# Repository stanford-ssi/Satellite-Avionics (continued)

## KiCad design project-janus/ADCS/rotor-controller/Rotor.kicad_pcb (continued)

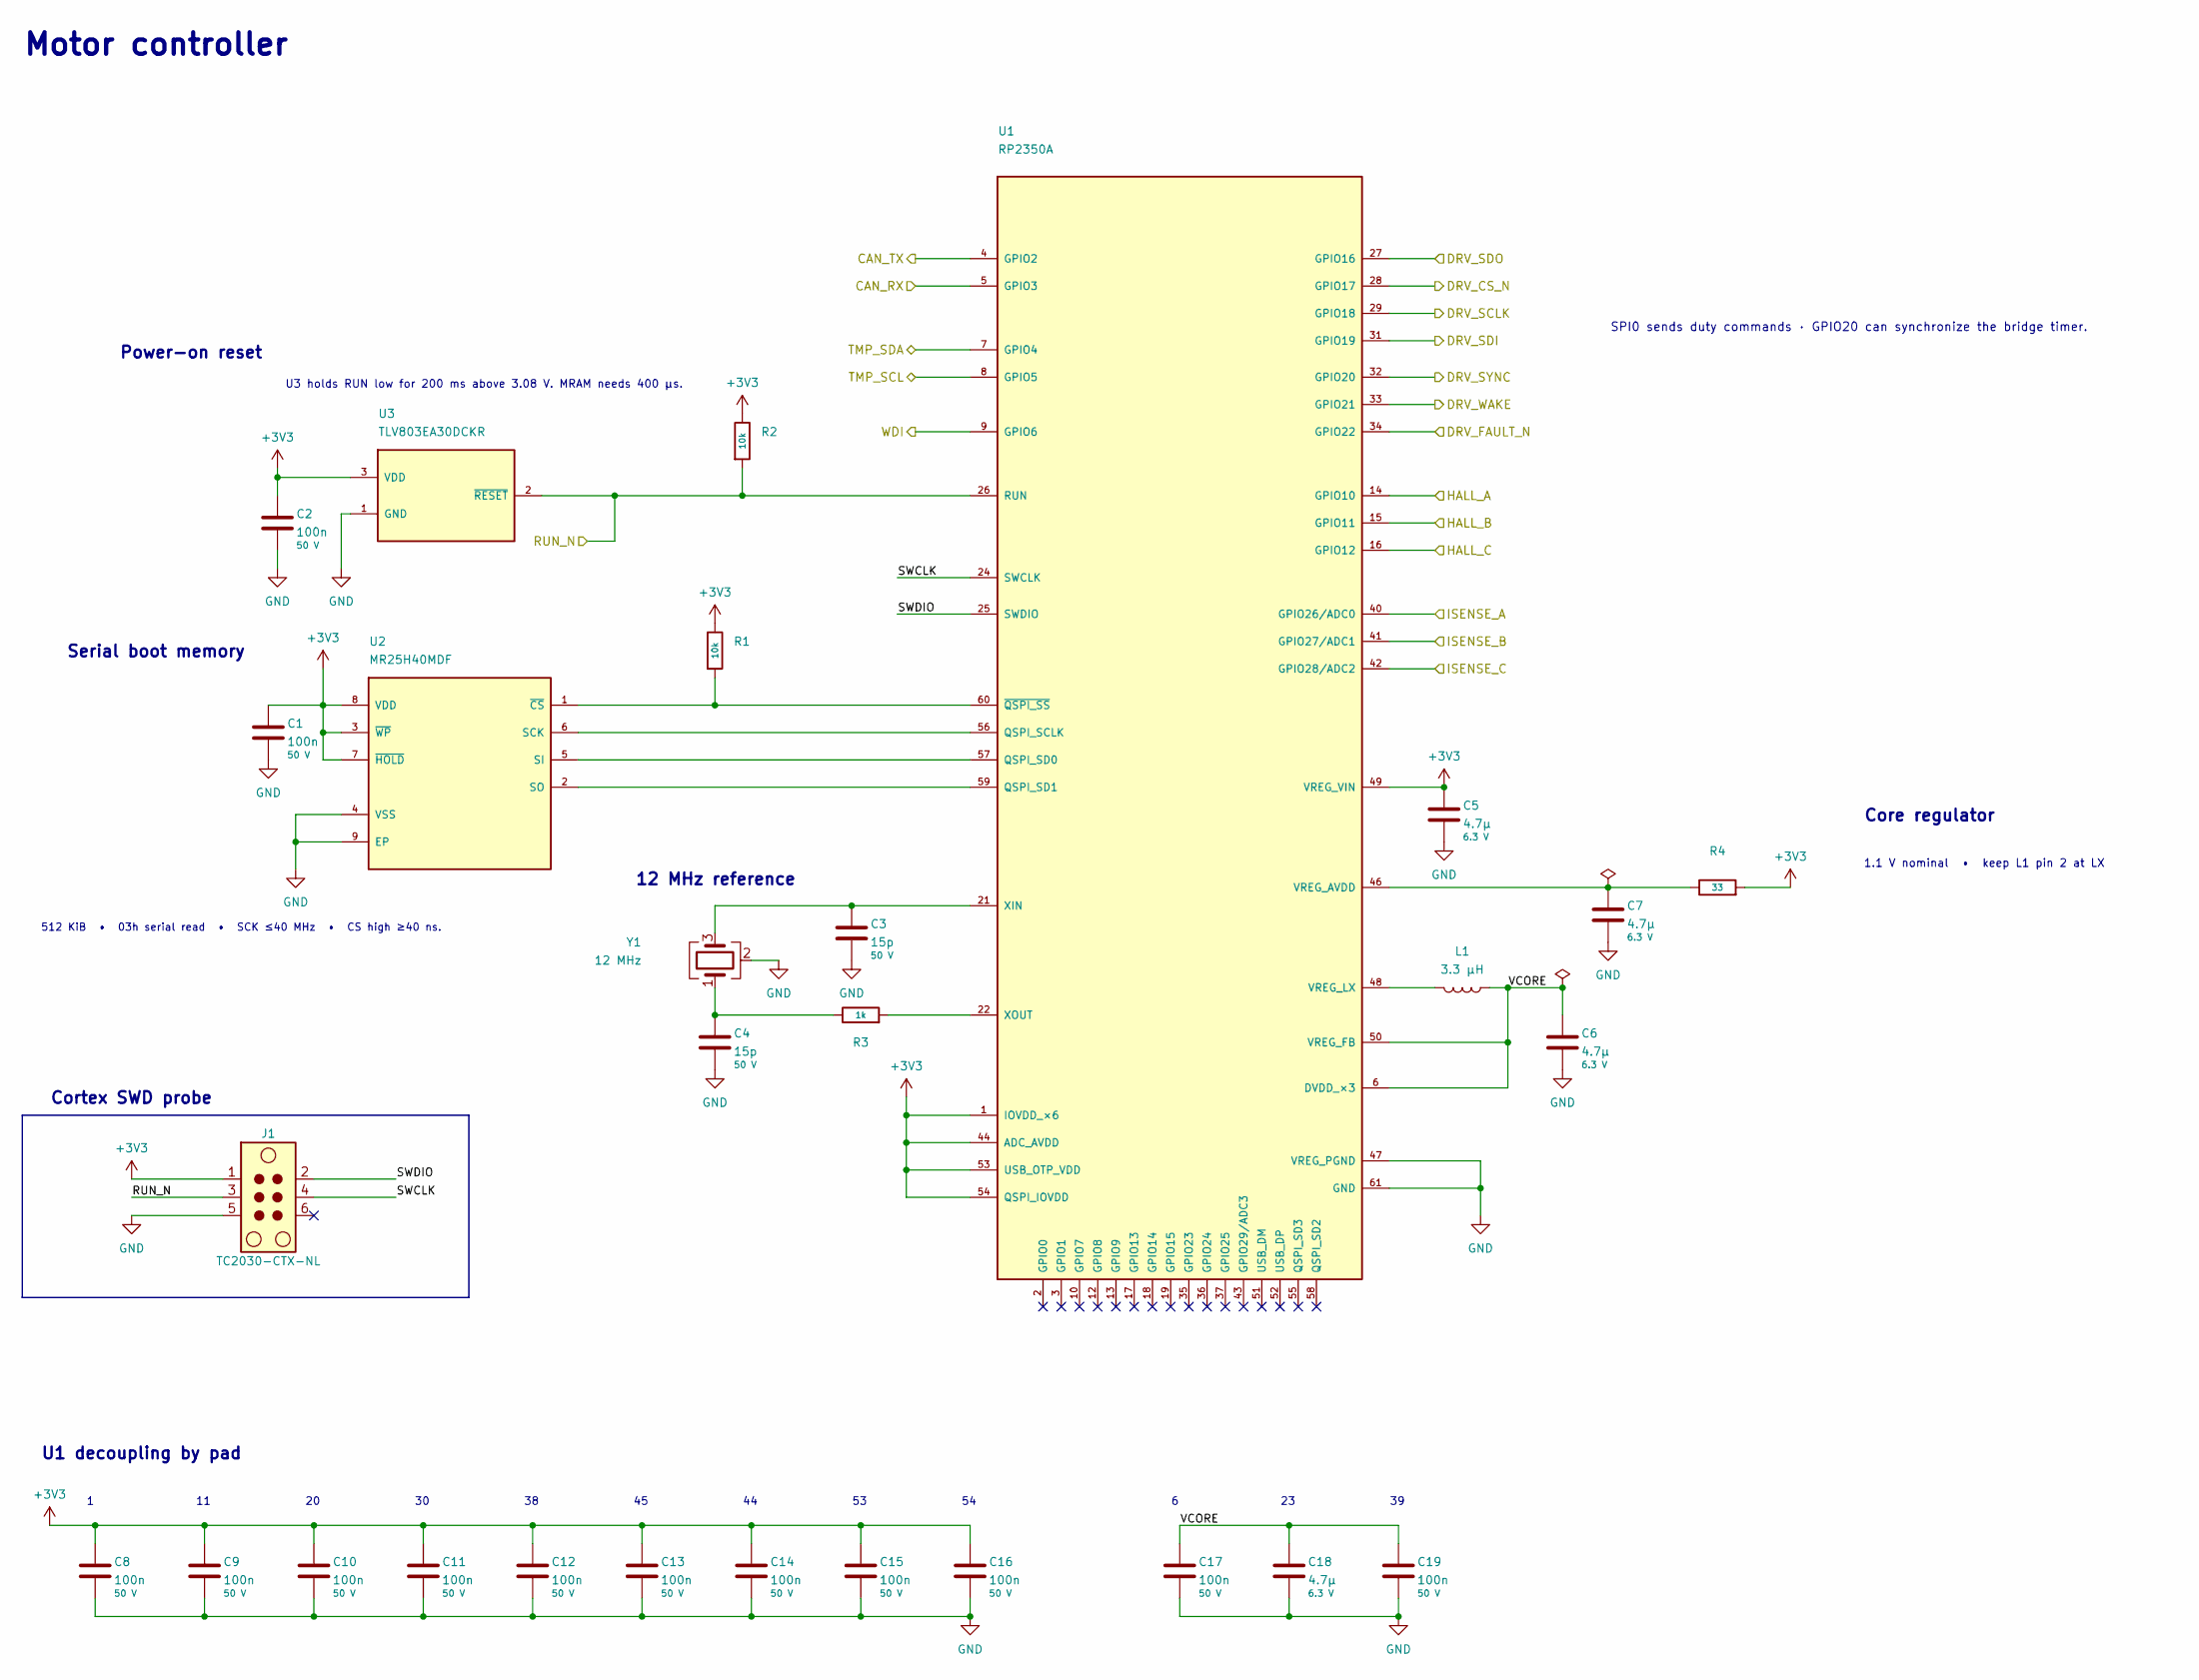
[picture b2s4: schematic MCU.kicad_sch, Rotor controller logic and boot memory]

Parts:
C1, C2, C8, C9, C10, C11, C12, C13, C14, C15, C16, C19: 100n; C_0402_1005Metric; Rating 50 V; Voltage 50 V; MPN GCM155R71H104KE02D
C3, C4: 15p; C_0402_1005Metric; Rating 50 V C0G, ±1%; Voltage 50 V; MPN GCM1555C1H150FA16D
C5, C6: 4.7µ; C_0402_RP2350_VREG; Rating 6.3 V X5R; Voltage 6.3 V; MPN GRM155R60J475ME47D
C7, C18: 4.7µ; C_0402_1005Metric; Rating 6.3 V X5R; Voltage 6.3 V; MPN GRM155R60J475ME47D
C17: 100n; C_0402_1005Metric_NoSilk; Rating 50 V; Voltage 50 V; MPN GCM155R71H104KE02D
J1: TC2030-CTX-NL; Tag-Connect_TC2030-IDC-NL_2x03_P1.27mm_Vertical
L1: 3.3 µH; Abracon_AOTA_B201610S3R3_101_T; Rating 3.3 µH; 2.1 A; 2.4 A saturation; MPN AOTA-B201610S3R3-101-T
R1, R2: 10k; R_0402_1005Metric; Rating 50 V, 0.063 W at 70 °C; MPN CRCW040210K0FKED
R3: 1k; R_0402_1005Metric; Rating 50 V, ±0.1%; MPN TNPW04021K00BEED
R4: 33; R_0402_1005Metric; Rating 50 V, ±0.5%; MPN TNPW040233R0DEED
U1: RP2350A; QFN-60-1EP_7x7mm_P0.4mm_EP3.4x3.4mm; MPN SC1509-A4
U2: MR25H40MDF; MPN MR25H40MDF
U3: TLV803EA30DCKR; TI_DCK0003A_SC-70-3; MPN TLV803EA30DCKR
Y1: 12 MHz; Abracon_ABM8_3225_4Pad; Rating 12 MHz, 10 pF load, ±30 ppm; MPN ABM8-272-T3

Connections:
+3V3: C1.1, C2.1, C5.1, C8.1, C9.1, C10.1, C11.1, C12.1, C13.1, C14.1, C15.1, C16.1, J1.1, R1.1, R2.1, R4.2, U1.1 (IOVDD_×6), U1.11 (IOVDD), U1.20 (IOVDD), U1.30 (IOVDD), U1.38 (IOVDD), U1.44 (ADC_AVDD), U1.45 (IOVDD), U1.49 (VREG_VIN), U1.53 (USB_OTP_VDD), U1.54 (QSPI_IOVDD), U2.3 (~WP), U2.7 (~HOLD), U2.8 (VDD), U3.3 (VDD); also elsewhere on the board
/CAN and housekeeping/CAN_RX: U1.5 (GPIO3); also elsewhere on the board
/CAN and housekeeping/CAN_TX: U1.4 (GPIO2); also elsewhere on the board
/CAN and housekeeping/TMP_SCL: U1.8 (GPIO5); also elsewhere on the board
/CAN and housekeeping/TMP_SDA: U1.7 (GPIO4); also elsewhere on the board
/CAN and housekeeping/WDI: U1.9 (GPIO6); also elsewhere on the board
/Motor control/DRV_CS_N: U1.28 (GPIO17); also elsewhere on the board
/Motor control/DRV_FAULT_N: U1.34 (GPIO22); also elsewhere on the board
/Motor control/DRV_SCLK: U1.29 (GPIO18); also elsewhere on the board
/Motor control/DRV_SDI: U1.31 (GPIO19); also elsewhere on the board
/Motor control/DRV_SDO: U1.27 (GPIO16); also elsewhere on the board
/Motor control/DRV_SYNC: U1.32 (GPIO20); also elsewhere on the board
/Motor control/DRV_WAKE: U1.33 (GPIO21); also elsewhere on the board
/Motor control/HALL_A: U1.14 (GPIO10); also elsewhere on the board
/Motor control/HALL_B: U1.15 (GPIO11); also elsewhere on the board
/Motor control/HALL_C: U1.16 (GPIO12); also elsewhere on the board
/Motor control/ISENSE_A: U1.40 (GPIO26/ADC0); also elsewhere on the board
/Motor control/ISENSE_B: U1.41 (GPIO27/ADC1); also elsewhere on the board
/Motor control/ISENSE_C: U1.42 (GPIO28/ADC2); also elsewhere on the board
/Motor control/RUN_N: J1.3, R2.2, U1.26 (RUN), U3.2 (~RESET); also elsewhere on the board
/Motor control/SWCLK: J1.4, U1.24 (SWCLK)
/Motor control/SWDIO: J1.2, U1.25 (SWDIO)
/Motor control/VCORE: C6.1, C17.1, C18.1, C19.1, L1.1, U1.6 (DVDD_×3), U1.23 (DVDD), U1.39 (DVDD), U1.50 (VREG_FB)
GND: C1.2, C2.2, C3.2, C4.2, C5.2, C6.2, C7.2, C8.2, C9.2, C10.2, C11.2, C12.2, C13.2, C14.2, C15.2, C16.2, C17.2, C18.2, C19.2, J1.5, U1.47 (VREG_PGND), U1.61 (GND), U2.4 (VSS), U2.9 (EP), U3.1 (GND), Y1.2 (G), Y1.4 (G); also elsewhere on the board
unnamed: C4.1, R3.1, Y1.1
unnamed: U1.56 (QSPI_SCLK), U2.6 (SCK)
unnamed: U1.57 (QSPI_SD0), U2.5 (SI)
unnamed: U1.59 (QSPI_SD1), U2.2 (SO)
unnamed: C7.1, R4.1, U1.46 (VREG_AVDD)
unnamed: L1.2, U1.48 (VREG_LX)
unnamed: C3.1, U1.21 (XIN), Y1.3
unnamed: R3.2, U1.22 (XOUT)
unnamed: R1.2, U1.60 (~QSPI_SS), U2.1 (~CS)

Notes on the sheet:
1.1 V nominal • keep L1 pin 2 at LX
U3 holds RUN low for 200 ms above 3.08 V. MRAM needs 400 µs.
512 KiB • 03h serial read • SCK ≤40 MHz • CS high ≥40 ns.
U1 decoupling by pad
SPI0 sends duty commands · GPIO20 can synchronize the bridge timer.
12 MHz reference
Serial boot memory
Core regulator
Power-on reset
Motor controller
Cortex SWD probe

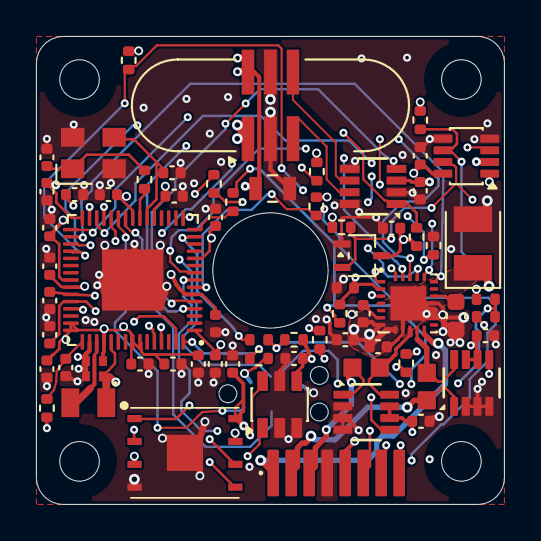
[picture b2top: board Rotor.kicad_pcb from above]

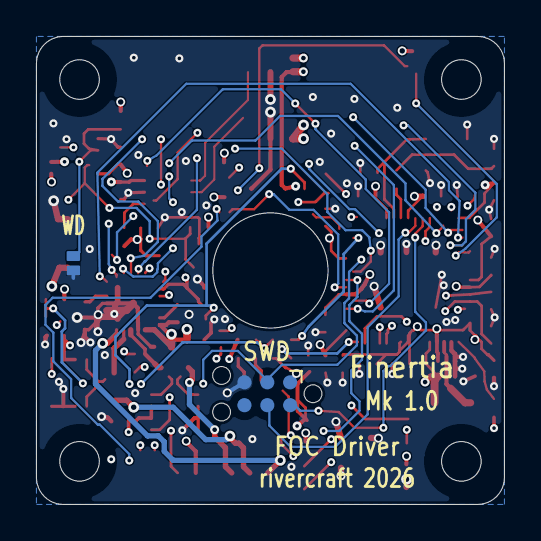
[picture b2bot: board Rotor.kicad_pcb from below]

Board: 6 copper layers, 26.0 x 26.0 mm, 71 parts (2 on the bottom side), 50 nets.

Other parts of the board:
M1: 2610T012B flange; Faulhaber_2610_Flange

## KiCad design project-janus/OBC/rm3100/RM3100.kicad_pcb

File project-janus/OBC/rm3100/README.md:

# RM3100 magnetometer board (Janus)

Primary magnetometer for ADCS: PNI RM3100 sensor suite (MagI2C ASIC, 2x Sen-XY-f, 1x Sen-Z-f)
on a small remote board, mounted >= 8 cm from torquers and reaction wheels (location TBD with Structures, 11/9 systems meeting allocated in the corner opposite of magnetorquers).

- Power: switched, current-monitored 3V3_MAG from the OBC over the J_MAG harness (proposed, unconfirmed).
- Connects to: OBC via 8-pin J_MAG harness: SPI mode 0, max 1 MHz, plus DRDY.
- Measures: 3-axis magnetic field for B-dot detumble and attitude determination. Backup: MMC5983MA on the OBC.

Design Master link: https://docs.google.com/spreadsheets/d/1Magy7Pv5RpWoOE26eidlDhtyJ_tfjOZqjaHxG35c-vI/edit?usp=sharing

Status: schematic in progress. Owner: Marlon Moenius.

## Datasheets

| File | Document | Doc no. | Rev | Retrieved |
|---|---|---|---|---|
| `datasheets/RM3100_1017252_r06.pdf` | RM3100 & RM2100 Sensor Suite User Manual (PNI Sensor) | 1017252 | r06 | 2026-11-11 |

Values used from this revision: R_bias = 121 Ω, R_EXT = 33 kΩ (Table 3-1, p. 5, specified at 3.0 V);
pin table (§4.3, p. 19); SPI reference schematic (Fig. 4-1, p. 15); coil orientation (§4.2.1 and Fig. 4-4, pp. 17–18);
pad layouts (Fig. 3-3 p. 9, Fig. 3-6 p. 11); MagI2C package (Fig. 3-7 p. 12).
Assembly: PNI sensor coils require halide-free solder paste and processes (§3.5, p. 13).

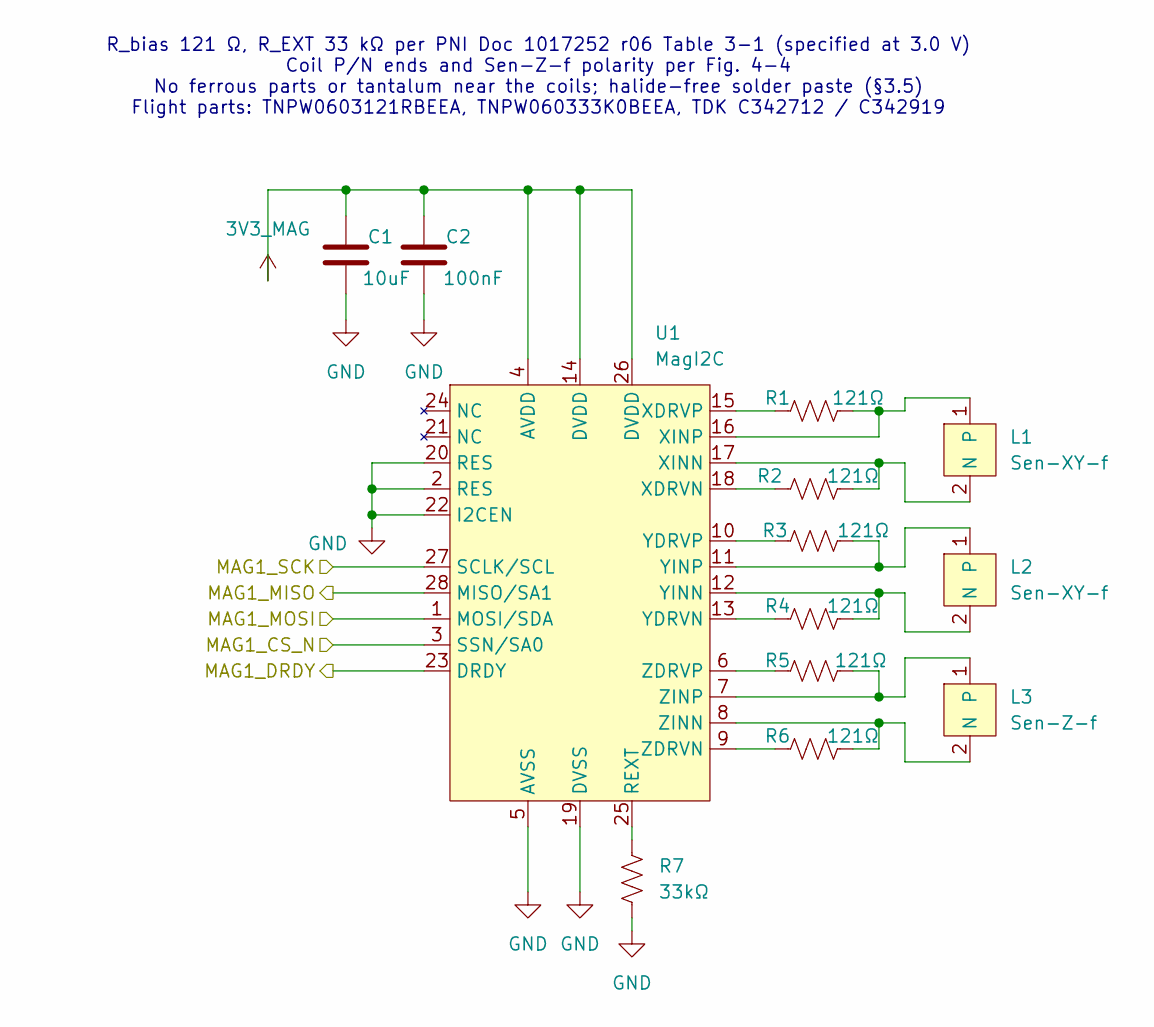
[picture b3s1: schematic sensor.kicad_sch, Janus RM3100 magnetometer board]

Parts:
C1: 10uF; C_0805_2012Metric; Voltage 25V; Tolerance 10%; MPN CL21A106KAYNNNE; LCSC C15850
C2: 100nF; C_0805_2012Metric; Voltage 100V; Tolerance 10%; MPN CL21B104KCFNNNE; LCSC C28233
L1, L2: Sen-XY-f; Manufacturer PNI Sensor
L3: Sen-Z-f; Manufacturer PNI Sensor
R1, R2, R3, R4, R5, R6: 121Ω; R_0603_1608Metric; Tolerance 1%; Voltage 75V; MPN 0603WAF1210T5E; LCSC C22867
R7: 33kΩ; R_0603_1608Metric; Tolerance 1%; Voltage 75V; MPN 0603WAF3302T5E; LCSC C4216
U1: MagI2C; PNI_MagI2C_MLF-28_4x4mm_P0.4mm; Manufacturer PNI Sensor

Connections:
3V3_MAG: C1.1, C2.1, U1.4 (AVDD), U1.14 (DVDD), U1.26 (DVDD); also elsewhere on the board
/Connector & protection/MAG1_CS_N: U1.3 (SSN/SA0); also elsewhere on the board
/Connector & protection/MAG1_DRDY: U1.23 (DRDY); also elsewhere on the board
/Connector & protection/MAG1_MISO: U1.28 (MISO/SA1); also elsewhere on the board
/Connector & protection/MAG1_MOSI: U1.1 (MOSI/SDA); also elsewhere on the board
/Connector & protection/MAG1_SCK: U1.27 (SCLK/SCL); also elsewhere on the board
GND: C1.2, C2.2, R7.2, U1.2 (RES), U1.5 (AVSS), U1.19 (DVSS), U1.20 (RES), U1.22 (I2CEN); also elsewhere on the board
unnamed: L1.2 (N), R2.2, U1.17 (XINN)
unnamed: L1.1, R1.2, U1.16 (XINP)
unnamed: L2.2 (N), R4.2, U1.12 (YINN)
unnamed: L2.1, R3.2, U1.11 (YINP)
unnamed: L3.2 (N), R6.2, U1.8 (ZINN)
unnamed: L3.1, R5.2, U1.7 (ZINP)
unnamed: R7.1, U1.25 (REXT)
unnamed: R2.1, U1.18 (XDRVN)
unnamed: R1.1, U1.15 (XDRVP)
unnamed: R4.1, U1.13 (YDRVN)
unnamed: R3.1, U1.10 (YDRVP)
unnamed: R6.1, U1.9 (ZDRVN)
unnamed: R5.1, U1.6 (ZDRVP)

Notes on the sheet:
R_bias 121 Ω, R_EXT 33 kΩ per PNI Doc 1017252 r06 Table 3-1 (specified at 3.0 V) Coil P/N ends and Sen-Z-f polarity per Fig. 4-4 No ferrous parts or tantalum near the coils; halide-free solder paste (§3.5) Flight parts: TNPW0603121RBEEA, TNPW060333K0BEEA, TDK C342712 / C342919

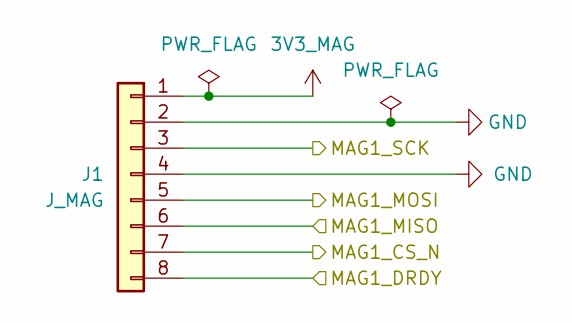
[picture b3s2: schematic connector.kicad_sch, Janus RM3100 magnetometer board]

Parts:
J1: J_MAG; PinHeader_1x08_P1.27mm_Vertical

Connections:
3V3_MAG: J1.1; also elsewhere on the board
/Connector & protection/MAG1_CS_N: J1.7; also elsewhere on the board
/Connector & protection/MAG1_DRDY: J1.8; also elsewhere on the board
/Connector & protection/MAG1_MISO: J1.6; also elsewhere on the board
/Connector & protection/MAG1_MOSI: J1.5; also elsewhere on the board
/Connector & protection/MAG1_SCK: J1.3; also elsewhere on the board
GND: J1.2, J1.4; also elsewhere on the board

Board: 2 copper layers, 14 parts (0 on the bottom side), 20 nets, no tracks yet.

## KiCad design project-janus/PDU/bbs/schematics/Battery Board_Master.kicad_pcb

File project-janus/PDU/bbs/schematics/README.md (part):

# Battery Board System (BBS)

> This README mirrors the Battery Board System (BBS) section of PJ-100002 (PDU Architecture & Design). Both are generated from `docs/build/make_section.js`; edit that file and rebuild so they stay in sync.

**Responsible Engineer:  Alessandro Gregori**

**Requirements:** [H-05] [H-11] [H-12]

**Topology:** 2× 2S 18650 strings → polyfuse per string → LTC4353 ideal-diode OR (one SQS460EN per string) → VBAT_RAW → J_EXT1 to PDU

**Charging (per string):** CHG_IN from the BCDR → LTC4412 + Si7625DN charge ideal diode → 1.5 A fuse → string

**Heater loop (per string):** NTC divider → MCP65R46 comparator (with hysteresis) → FPF2700 ON pin → heater on J_Heat

## Board Function

The battery board is the satellite's energy store. It holds four 18650 Li-ion cells as two independent 2S strings (7.4 V nominal, 8.4 V full, 6.0 V cutoff) and delivers one combined battery rail, **VBAT_RAW**, to the PDU, which charges the pack (SACD/BCDR) and distributes it to loads (VLSA).

The board does three things on its own, with no software:

- **Stores energy and protects each string.** Each string has its own resettable fuse, so a hard short inside one string is cut off from the rest of the board.
- **Combines the strings without letting them fight.** An ideal-diode controller passes current from whichever string is higher onto VBAT_RAW, and blocks current from flowing back into a string. A weak, shorted or disconnected string simply drops out, and the healthy string keeps the satellite running. This is why the two strings are ORed instead of wired directly in parallel (the same reasoning OreSat uses for its separate 2S packs [2]).
- **Keeps the cells warm enough to charge.** Li-ion cells must not be charged below about 0 °C. Each string has a thermistor and a comparator thermostat that switch a Kapton film heater, wrapped directly on that string's cells, on below about 5.7 °C and off above about 14.7 °C. The heater is powered from its own string and current-limited, so a heater fault can't drain the pack.

### How it behaves

- **Normal:** both strings share the load; the ideal diodes keep the drop to tens of millivolts.
- **One string low or failed open:** its MOSFET turns off and the other string carries the bus alone.
- **Short inside a string:** the polyfuse trips, and the ideal diode stops the good string from feeding the short.
- **Cold pack:** the thermostat turns that string's heater on below ~5.7 °C and back off above ~14.7 °C.
- **Shorted heater:** the FPF2700 limits current to ~0.5 A and auto-restarts, so the string keeps powering the bus.
- **PDU MCU off or resetting:** heaters and ORing keep working; only the 3.3 V thermostat supply comes from the PDU.

*Battery board block diagram: power path in blue, ORing in red, heater control in orange.*

### Board build

- 2-layer FR-4, 1.6 mm, 99.5 × 140.5 mm outline; all 40 parts on the top side
- Channel A and channel B (strings, heater switches, thermostats) are laid out as mirror images about the board centre line, so both channels see the same trace lengths and thermal environment
- Cells sit in four Keystone 1042 surface-mount 18650 holders; ground and power use copper pours (2 zones), 282 track segments, 171 vias
- Connectors: J_EXT1 (Molex Micro-Fit 3.0, 5-pin: CHG_IN_A, VBAT_RAW, 3V3, GND, CHG_IN_B) to the PDU; J_Heat_A and J_Heat_B (JST PH) to the heaters
- Schematic is hierarchical: a master sheet with six sub-sheets: Batteries, Dual Ideal Diode (discharge ORing), Charge Path A, Charge Path B, Heater A, Heater B

### Ideal diode controller: LTC4353IMS#PBF

<https://www.analog.com/media/en/technical-documentation/data-sheets/4353f.pdf>

- Dual controller, 0–18 V ORing, so one IC covers both strings; −40 to 85 °C (I-grade); MSOP-16
- Gate clamped 12 V above input, so the FETs are fully enhanced at 2S; tens of mV drop vs ~0.4 V for a Schottky
- **Heritage:** no record of the LTC4353 itself flying. Its single-channel sibling, the LTC4352, flew on Quetzal-1 (1U, 2020) as the battery-path ideal diode [1]
- Not stocked at LCSC (DigiKey/Mouser); confirm it's still active before freezing the design

### ORing MOSFET: SQS460EN-T1_GE3 (Vishay, AEC-Q101)

<https://www.vishay.com/docs/72642/sqs460en.pdf>

- 60 V N-channel, 36 mΩ max @ 10 V (30 mΩ typ), C_iss 603 pF typ / 755 pF max, PowerPAK 1212-8; replaces the Si4126DY for its radiation data
- **Heritage:** NASA GSFC heavy-ion single-event testing (NSREC 2017) [15]; failures (burnout) only at drain voltages far above our 8.4 V bus. NASA also notes large part-to-part variation, so screen a sample
- Conduction loss: (2 A)² × 36 mΩ = **0.14 W**; (3 A)² × 36 mΩ = **0.32 W**; at 125 °C R_DS(on) rises to 66 mΩ. Keep each string at about **3 A or less**; the Si4126DY (2.75 mΩ) is the low-loss fallback if the load budget needs more
- Schematic symbol Transistor_FET:SiS454DN with the stock footprint Package_SO:Vishay_PowerPAK_1212-8_Single: pins 1-3 = S, 4 = G, 5 (pins 5-8 + exposed pad) = D, the same pinout as the SQS460EN

### Heater switch: FPF2700MX (onsemi)

<https://www.onsemi.cn/pub/Collateral/FPF2702CN-D.pdf>

- 2.8–36 V load switch, current limit set by R_SET (0.4–2 A), 88 mΩ, SOIC-8; ON is active-LOW
- Auto-restart after a fault (FPF2701 latches off), so a heater fault recovers without software
- R_SET = 549 kΩ → I_LIM = 277.5 / 549 = **0.51 A typ / 0.40 A min** (datasheet table value, 1 %)
- **Heritage:** flew on MIT's MicroMAS CubeSat and was total-dose tested to 8 and 24 krad(Si), far above a typical 1.2 krad LEO dose [4]

### Thermostat: MCP65R46T-1202E/CHY + NASA 44907 NTC

- ~3 µA open-drain comparator on 3.3 V, SOT-23-6; threshold set by a divider so it's ratiometric with the NTC divider
- R_NTC = 10 kΩ (= NTC at 25 °C) → 1.65 V at 25 °C, most sensitive point; 165 µA
- Threshold: 150k / 300k → V+ = 2.20 V → trips at 20 kΩ ≈ **8.7 °C**
- Thermistor: YSI/TE **44907 = NASA GSFC S-311-P-18/07S7R6**, 10 kΩ at 25 °C, β = 3574 K, ±0.2 °C, −55 to +90 °C, outgassing 0.66 % TML / 0.01 % CVCM [16][17]. Leaded: the bead is bonded to the string's cells and the leads solder to two pads on the board, so it reads cell temperature
- 1.0 MΩ feedback adds hysteresis: heater ON below ≈ **5.7 °C** (V+ = 2.30 V, R_th > 23.0 kΩ), OFF above ≈ **14.7 °C** (V+ = 2.00 V, R_th < 15.4 kΩ). 1.0 MΩ was chosen over 1.2 MΩ because TNPW0805 tops out at 1 MΩ
- 10 kΩ pull-up holds ON high (heater off) until the comparator sinks it; standby ≈ **0.18 mA per channel** on 3.3 V
- **Heritage:** the 44907 is a NASA-qualified (S-311-P-18 QPL) part [16]. No flight or radiation data found for the MCP65R46; keep it in the radiation/TVAC test plan (TI TLV1704-SEP is a radiation-tolerant alternative if the comparator is ever changed)

### Charge path (per string): LTC4412 + Si7625DN + 1206L150

- CHG_IN (a regulated CC/CV charge output from the BCDR, 8.4 V max) → Si7625DN P-channel FET → 1.5 A fuse → BTx+. One circuit per string, on its own sheet
- LTC4412 turns the FET fully on when CHG_IN is ~20 mV above the string and off when the string is higher, so current only flows into the string and the strings never feed each other; CTL tied to GND (automatic), STAT unused
- The ideal diode only steers: charge voltage/current regulation and the charge stop belong to the BCDR (the FET's body diode still conducts when off)
- **Heritage:** the same LTC4412 + Si7625DN + 1206L150 charge path flew on OreSat0's 2S battery card [18]

### Per-string fuse: Littelfuse 1206L500/12SLPR

- 5 A hold, 12 V, 1206 PPTC; the same part OreSat0 flew on its 2S battery discharge path [18]
- Clears a hard short inside a string; the ideal diodes keep the other string on the bus. PPTC trip current shifts with temperature, so check it across −40 to +80 °C

### Cells: LG INR18650-MJ1 (3,500 mAh)

- NASA JPL/JSC/KSC testing found MJ1 had the highest specific energy of the cells tested (>230 Wh/kg at 20 °C), ~90 % capacity after 1,100 cycles, and was the best performer at 0 °C [5]
- Flight heritage on NASA's PACE mission (NASA SmallSat State-of-the-Art) [6]; selected for Europa Clipper [5]
- Standard cell in Pumpkin's BM 2 CubeSat battery module, which meets JSC EP-WI-032 for ISS deployment [7]; also used on the PyCubed battery board [8]
- At −20 °C its output drops to 30–70 Wh/kg [5], which is why the heaters matter

### LTC4353 support caps

- C_CPO = 10 nF (CGA3E2X7R1H103K080AA): datasheet says ~10× MOSFET C_iss; 10 nF ≈ 13× the SQS460EN's 755 pF max
- C_VCC = 0.1 µF (required); C_V_OUT = 10 µF on VBAT_RAW (datasheet recommended, limits switchover droop)

## 3.3 V Power Budget (external rail from the PDU)

The board draws **under 1 mA (about 3 mW worst case)** from the PDU's 3.3 V on J_EXT1 pin 3. Only the two heater thermostats use it; the LTC4353, LTC4412s and FPF2700s are powered from the battery strings, and the heaters themselves run from the strings (≈ 2.8 W each), not from 3.3 V.

### What is on the 3.3 V rail (per heater channel)

- **MCP65R46 comparator (U2 / U3):** 2.5 µA typical, 4 µA maximum quiescent current [19]
- **NTC divider (R_NTC 10 kΩ + 44907 thermistor):** 3.3 V / (10 kΩ + R_th); largest when the pack is hot (R_th falls)
- **Threshold divider (150 kΩ / 300 kΩ, with the 1 MΩ hysteresis resistor):** ≈ 7.7 µA (heater off) to 8.7 µA (heater on)
- **Pull-up (R_PullUp 10 kΩ):** 0.33 mA only while the comparator holds the heater on (output low); ~0 when the heater is off
- **C_OP 100 nF and the FPF2700 ON input:** no DC current (ON input leakage is negligible)

| Operating state (per channel) | NTC divider | Thresh. divider | Pull-up | MCP65R46 | Channel total | Both channels |
| --- | --- | --- | --- | --- | --- | --- |
| Heater off, 25 °C (typical) | 165 µA | 7.7 µA | 0 | 2.5 µA | **175 µA** | **350 µA / 1.2 mW** |
| Heater off, 85 °C (hot worst case) | 291 µA | 7.7 µA | 0 | 4 µA | 303 µA | 605 µA / 2.0 mW |
| Heater on, at 5.7 °C turn-on (worst case) | 100 µA | 8.7 µA | 330 µA | 4 µA | **443 µA** | **886 µA / 2.9 mW** |
| Heater on, −40 °C | 11 µA | 8.7 µA | 330 µA | 4 µA | 354 µA | 708 µA / 2.3 mW |

**Budget to request from the PDU: 1 mA at 3.3 V (3.3 mW).** That covers the worst case (both heaters switching on at once, 886 µA) with about 10 % margin. The ICs themselves are tiny (2 × 4 µA max); the resistor networks dominate, mostly the 10 kΩ NTC divider and the pull-up while heating. If the 3.3 V budget ever gets tight, a 100 kΩ NTC + 100 kΩ R_NTC and a 100 kΩ pull-up would cut it roughly 10×, at the cost of more noise pickup.

Thermistor resistance uses the 44907's β = 3574 K: R_th = 1.34 kΩ at 85 °C, 22.9 kΩ at the 5.7 °C turn-on point, 283 kΩ at −40 °C. Comparator current is the datasheet maximum in the worst-case rows.

## Flight Heritage Summary

The architecture (battery board with its own heater and autonomous thermostat) is standard on flown CubeSat batteries. The ORing controller, MOSFET and thermostat parts are commercial parts without direct heritage.

| Part / feature | Heritage | Status |
| --- | --- | --- |
| Autonomous battery heater + thermostat | ISIS ICEPS2 (PEASSS 2016, Hiber 1/2 2018) [9]; GomSpace P31u/BP4 (GomX-1, FUNcube, Triton-1) [10]; AAC Clyde Space Optimus, >100 missions [11]; Quetzal-1 on-orbit [1] | Flown |
| 2S 18650 strings kept separate | OreSat 2× 2S1P packs [2]; ISIS ICEPS2 2S1P [9] | Flown / vendor |
| LG INR18650-MJ1 cells | NASA PACE [6]; Pumpkin BM 2 [7]; NASA cell testing [5] | Flown |
| FPF2700 load switch | MIT MicroMAS, TID tested to 24 krad [4] | Flown |
| LTC4353 ideal diode | Sibling LTC4352 flew on Quetzal-1 [1] | Family flown |
| SQS460EN MOSFET | NASA GSFC heavy-ion SEE test data [15] | Radiation-tested |
| 44907 thermistor | NASA GSFC S-311-P-18 qualified parts list [16] | NASA-qualified |
| MCP65R46 comparator | None found | Not flown |
| Kapton film heater on the cells | Pumpkin BM 2 [7]; OreSat battery board [2]; Quetzal-1 on-orbit [1]; most common small-spacecraft heater per NASA [13] | Flown |
| 1206L500 PPTC fuse | OreSat0 2S battery discharge path [18] | Flown |
| LTC4412 + Si7625DN + 1206L150 charge path | OreSat0 2S battery charge path [18] | Flown |

## Battery Heater: Kapton Polyimide Film

**Decision:** each 2S string gets its own Kapton (polyimide) etched-foil film heater, wrapped directly on that string's cells and plugged into J_Heat_A / J_Heat_B. It is shown on the schematic as HTR_A1 / HTR_B1 (BOM only, excluded from the PCB).

### Why Kapton

- Most flight heritage of any heater type: NASA's SmallSat State-of-the-Art calls Kapton heaters the most common on small spacecraft [13]
- Same approach as flown and vendor battery packs: Pumpkin BM 2 wraps a Kapton heater on each cell [7]; OreSat uses two 49 Ω Minco heaters in parallel (≈ 25 Ω, ≈ 2.8 W at 8.4 V) [2]; Quetzal-1 flew a 13 Ω Kapton heater between its cells and kept the pack from freezing at about a 25 % orbital duty cycle [1]
- Heat goes straight into the cell cans instead of crossing the PCB and the holder gap, which matters in vacuum where there is no air to carry heat
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
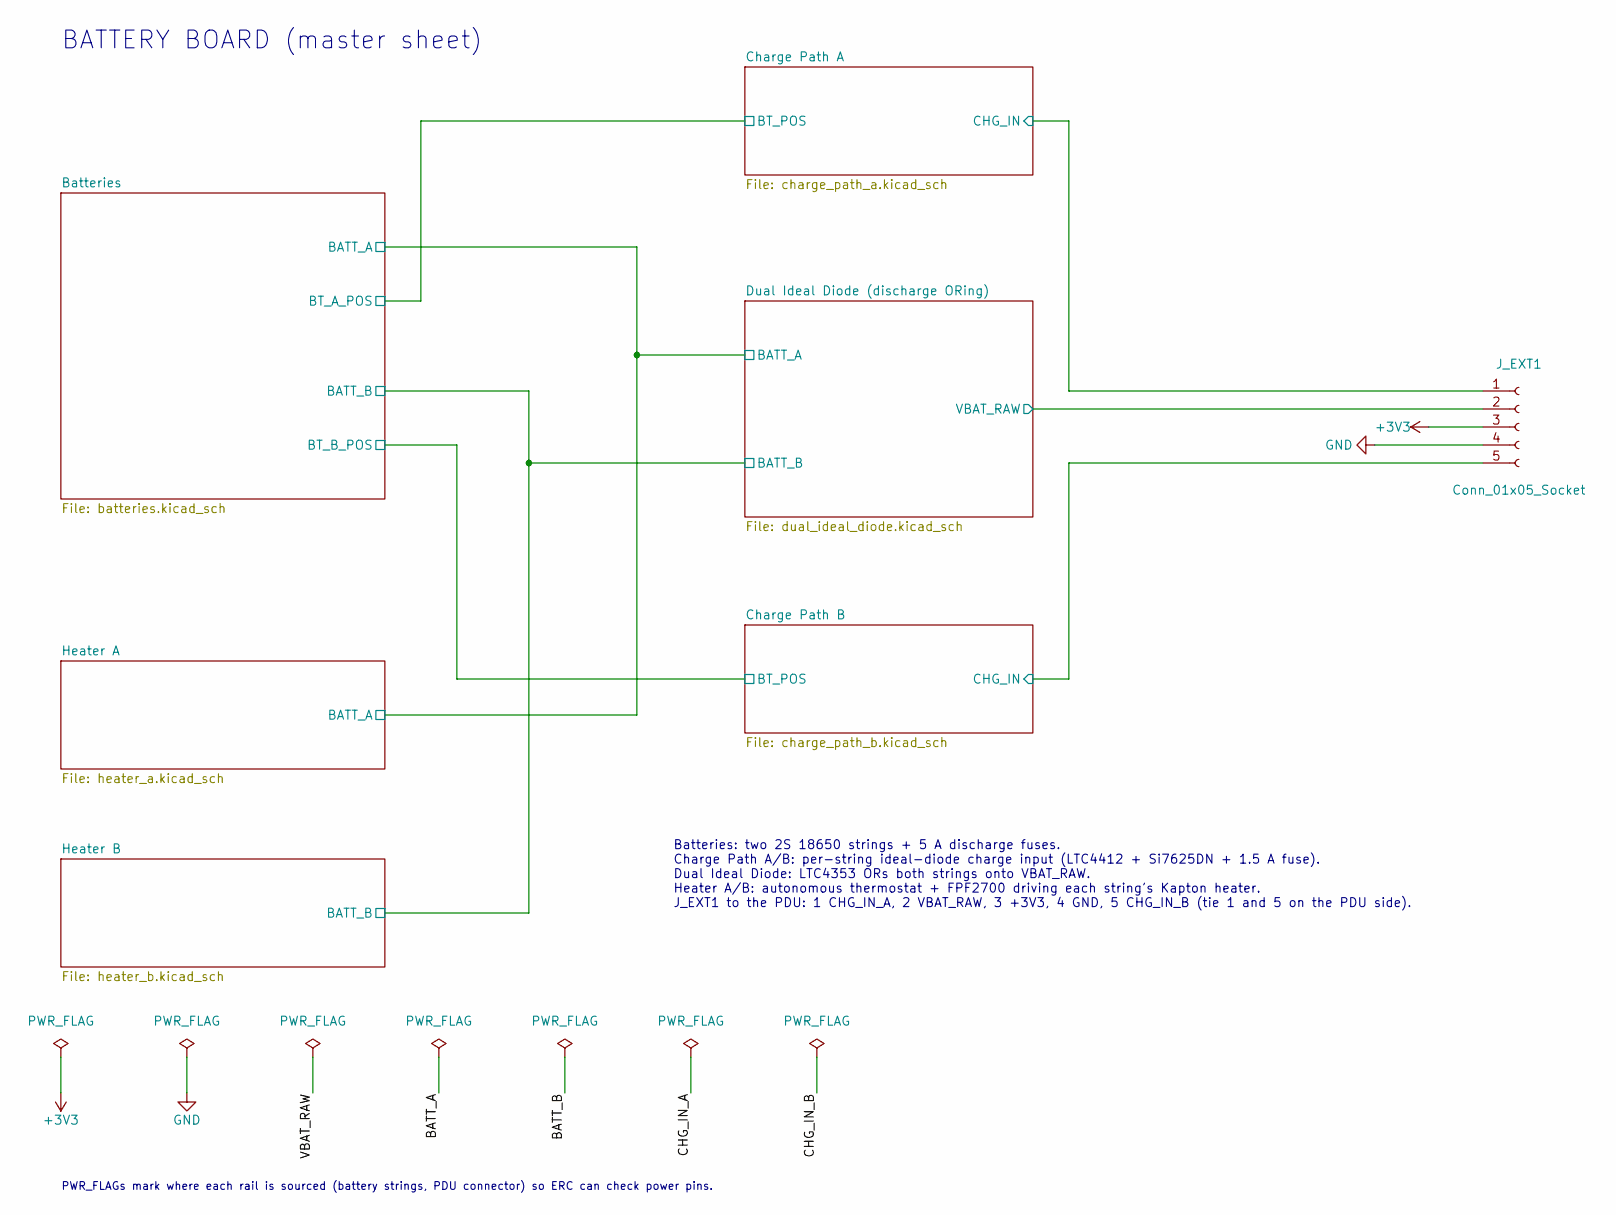
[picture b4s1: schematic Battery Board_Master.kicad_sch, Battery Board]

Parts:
J_EXT1: Conn_01x05_Socket; Molex_Micro-Fit_3.0_43650-0515_1x05_P3.00mm_Vertical; MPN 43650-0515; LCSC_PreFlight Verify at LCSC

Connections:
+3V3: J_EXT1.3; also elsewhere on the board
/Charge Path A/CHG_IN: J_EXT1.1; also elsewhere on the board
/Charge Path B/CHG_IN: J_EXT1.5; also elsewhere on the board
/Dual Ideal Diode (discharge ORing)/VBAT_RAW: J_EXT1.2; also elsewhere on the board
GND: J_EXT1.4; also elsewhere on the board

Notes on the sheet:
Batteries: two 2S 18650 strings + 5 A discharge fuses. Charge Path A/B: per-string ideal-diode charge input (LTC4412 + Si7625DN + 1.5 A fuse). Dual Ideal Diode: LTC4353 ORs both strings onto VBAT_RAW. Heater A/B: autonomous thermostat + FPF2700 driving each string's Kapton heater. J_EXT1 to the PDU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
PWR_FLAGs mark where each rail is sourced (battery strings, PDU connector) so ERC can check power pins.
BATTERY BOARD (master sheet)

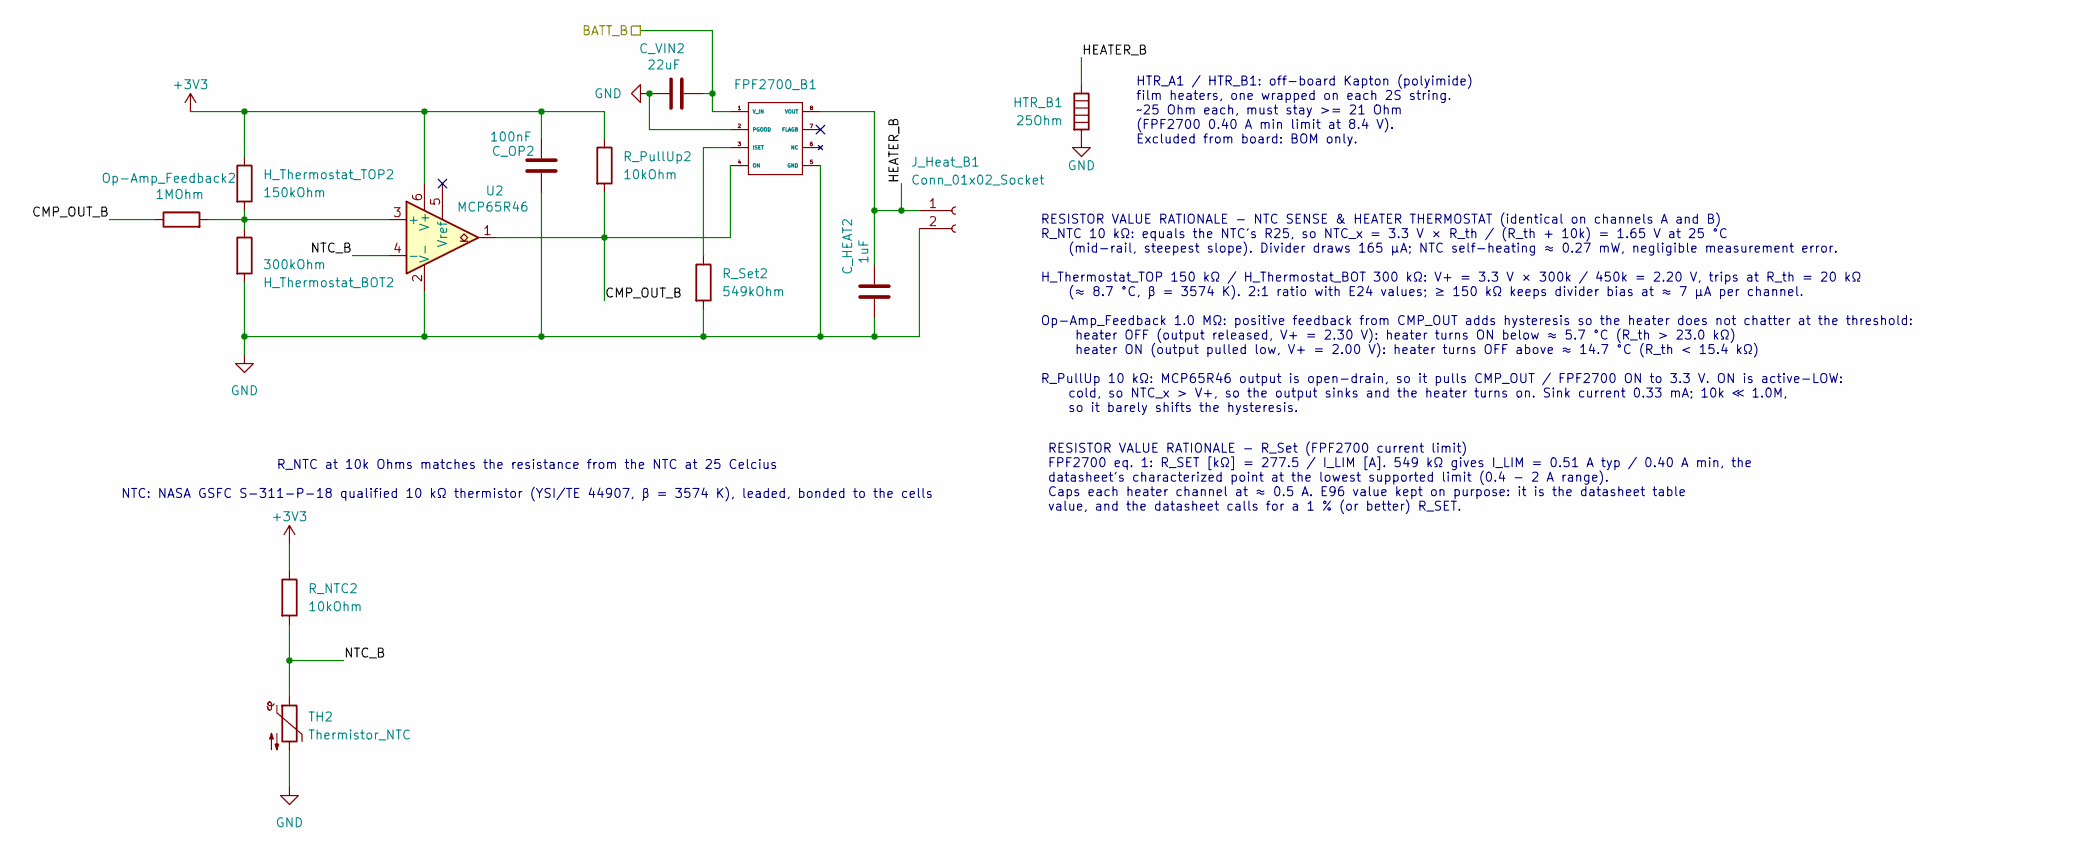
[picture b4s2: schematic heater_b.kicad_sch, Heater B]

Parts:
C_HEAT2: 1uF; C_0603_1608Metric; MPN CGA3E3X7R1H105K080AB; LCSC_PreFlight C15849
C_OP2: 100nF; C_0402_1005Metric; MPN GCM155R71H104KE02D; LCSC_PreFlight C1525
C_VIN2: 22uF; C_1206_3216Metric; MPN GRM31CC71E226ME15L; LCSC_PreFlight C12891
FPF2700_B1: SOIC-8_3.9x4.9mm_P1.27mm; MPN FPF2700MX; LCSC_PreFlight C328059
HTR_B1: 25Ohm; MPN TBD - Minco polyimide (Kapton) film hea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
H_Thermostat_BOT2: 300kOhm; R_0805_2012Metric; MPN TNPW0805300KBEEA; LCSC_PreFlight C17616
H_Thermostat_TOP2: 150kOhm; R_0805_2012Metric; MPN TNPW0805150KBEEA; LCSC_PreFlight C17470
J_Heat_B1: Conn_01x02_Socket; JST_PH_S2B-PH-SM4-TB_1x02-1MP_P2.00mm_Horizontal; MPN S2B-PH-SM4-TB(LF)(SN); LCSC_PreFlight C295747
Op-Amp_Feedback2: 1MOhm; R_0805_2012Metric; MPN TNPW08051M00BEEA; LCSC_PreFlight Verify at LCSC
R_NTC2: 10kOhm; R_0805_2012Metric; MPN TNPW080510K0BEEA; LCSC_PreFlight C17414
R_PullUp2: 10kOhm; R_0805_2012Metric; MPN TNPW080510K0BEEA; LCSC_PreFlight C17414
R_Set2: 549kOhm; R_0805_2012Metric; MPN TNPW0805549KBEEA; LCSC_PreFlight C17749
TH2: Thermistor_NTC; SolderWire-0.1sqmm_1x02_P3.6mm_D0.4mm_OD1mm; MPN 44907 (NASA GSFC S-311-P-18/07S7R6); LCSC_PreFlight N/A - DigiKey/Mouser
U2: MCP65R46; SOT-23-6; MPN MCP65R46T-1202E/CHY; LCSC_PreFlight Not stocked at LCSC - order from DigiKe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

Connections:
+3V3: C_OP2.1, H_Thermostat_TOP2.1, R_NTC2.1, R_PullUp2.1, U2.6 (V+); also elsewhere on the board
/Batteries/BATT_B: C_VIN2.2, FPF2700_B1.1 (V_IN); also elsewhere on the board
/Heater B/CMP_OUT_B: FPF2700_B1.4 (ON), Op-Amp_Feedback2.1, R_PullUp2.2, U2.1
/Heater B/HEATER_B: C_HEAT2.1, FPF2700_B1.8 (VOUT), HTR_B1.1, J_Heat_B1.1
/Heater B/NTC_B: R_NTC2.2, TH2.1, U2.4 (-)
GND: C_HEAT2.2, C_OP2.2, C_VIN2.1, FPF2700_B1.2 (PGOOD), FPF2700_B1.5 (GND), HTR_B1.2, H_Thermostat_BOT2.2, J_Heat_B1.2, R_Set2.2, TH2.2, U2.2 (V-); also elsewhere on the board
unnamed: FPF2700_B1.3 (ISET), R_Set2.1
unnamed: H_Thermostat_BOT2.1, H_Thermostat_TOP2.2, Op-Amp_Feedback2.2, U2.3 (+)

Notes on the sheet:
R_NTC at 10k Ohms matches the resistance from the NTC at 25 Celcius NTC: NASA GSFC S-311-P-18 qualified 10 kΩ thermistor (YSI/TE 44907, β = 3574 K), leaded, bonded to the cells
RESISTOR VALUE RATIONALE - NTC SENSE & HEATER THERMOSTAT (identical on channels A and B) R_NTC 10 kΩ: equals the NTC's R25, so NTC_x = 3.3 V × R_th / (R_th + 10k) = 1.65 V at 25 °C (mid-rail, steepest slope). Divider draws 165 µA; NTC self-heating ≈ 0.27 mW, negligible measurement error. H_Thermost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
RESISTOR VALUE RATIONALE - R_Set (FPF2700 current limit) FPF2700 eq. 1: R_SET [kΩ] = 277.5 / I_LIM [A]. 549 kΩ gives I_LIM = 0.51 A typ / 0.40 A min, the datasheet's characterized point at the lowest supported limit (0.4 - 2 A range). Caps each heater channel at ≈ 0.5 A. E96 value kept on purpose: 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
HTR_A1 / HTR_B1: off-board Kapton (polyimide) film heaters, one wrapped on each 2S string. ~25 Ohm each, must stay >= 21 Ohm (FPF2700 0.40 A min limit at 8.4 V). Excluded from board: BOM only.

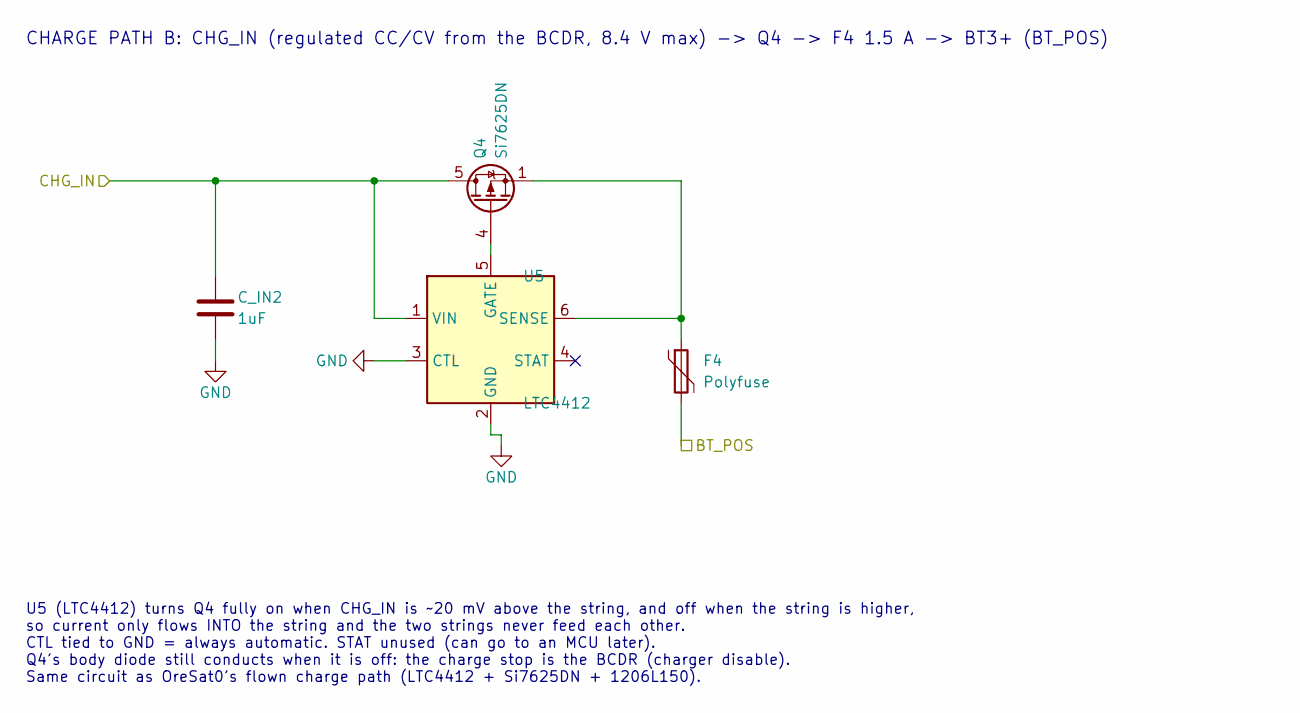
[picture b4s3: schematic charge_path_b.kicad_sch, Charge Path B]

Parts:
C_IN2: 1uF; C_0603_1608Metric; MPN CGA3E3X7R1H105K080AB
F4: Polyfuse; Fuse_1206_3216Metric; MPN 1206L150/12SLYR
Q4: Si7625DN; Vishay_PowerPAK_1212-8_Single; MPN SI7625DN-T1-GE3
U5: LTC4412; TSOT-23-6; MPN LTC4412ES6#TRPBF

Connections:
/Batteries/BT_B_POS: F4.2; also elsewhere on the board
/Charge Path B/CHG_IN: C_IN2.1, Q4.5 (D), U5.1 (VIN); also elsewhere on the board
GND: C_IN2.2, U5.2 (GND), U5.3 (CTL); also elsewhere on the board
unnamed: Q4.4 (G), U5.5 (GATE)
unnamed: F4.1, Q4.1 (S), Q4.2 (S), Q4.3 (S), U5.6 (SENSE)

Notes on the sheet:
CHARGE PATH B: CHG_IN (regulated CC/CV from the BCDR, 8.4 V max) -> Q4 -> F4 1.5 A -> BT3+ (BT_POS)
U5 (LTC4412) turns Q4 fully on when CHG_IN is ~20 mV above the string, and off when the string is higher, so current only flows INTO the string and the two strings never feed each other. CTL tied to GND = always automatic. STAT unused (can go to an MCU later). Q4's body diode still conducts when it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

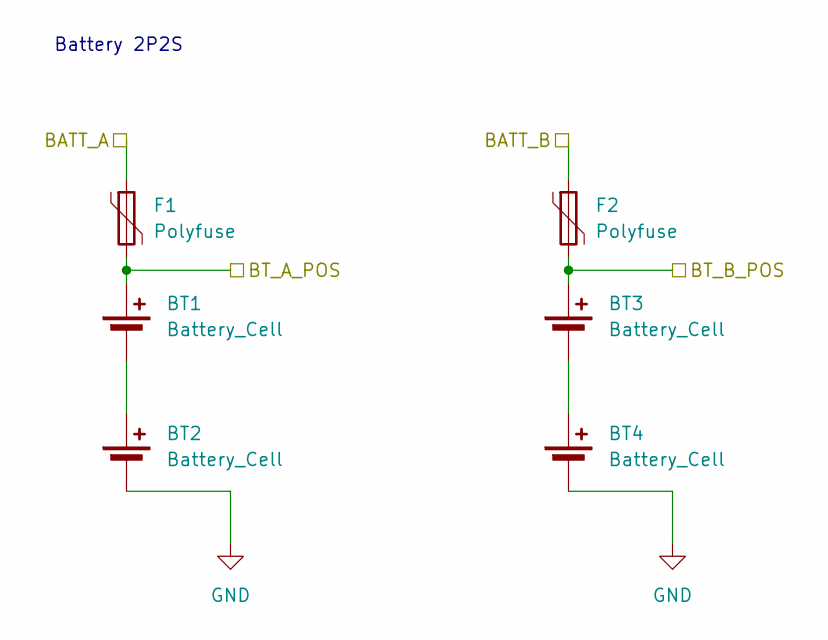
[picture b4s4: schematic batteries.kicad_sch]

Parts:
BT1, BT2, BT3, BT4: Battery_Cell; BatteryHolder_Keystone_1042_1x18650; MPN 1042 (holder) + INR18650-MJ1 (cell); LCSC_PreFlight Order from DigiKey/Mouser
F1, F2: Polyfuse; Fuse_1206_3216Metric; MPN 1206L500/12SLPR; LCSC_PreFlight Verify at LCSC

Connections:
/Batteries/BATT_A: F1.1; also elsewhere on the board
/Batteries/BATT_B: F2.1; also elsewhere on the board
/Batteries/BT_A_POS: BT1.1 (+), F1.2; also elsewhere on the board
/Batteries/BT_B_POS: BT3.1 (+), F2.2; also elsewhere on the board
GND: BT2.2 (-), BT4.2 (-); also elsewhere on the board
unnamed: BT1.2 (-), BT2.1 (+)
unnamed: BT3.2 (-), BT4.1 (+)

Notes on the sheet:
Battery 2P2S

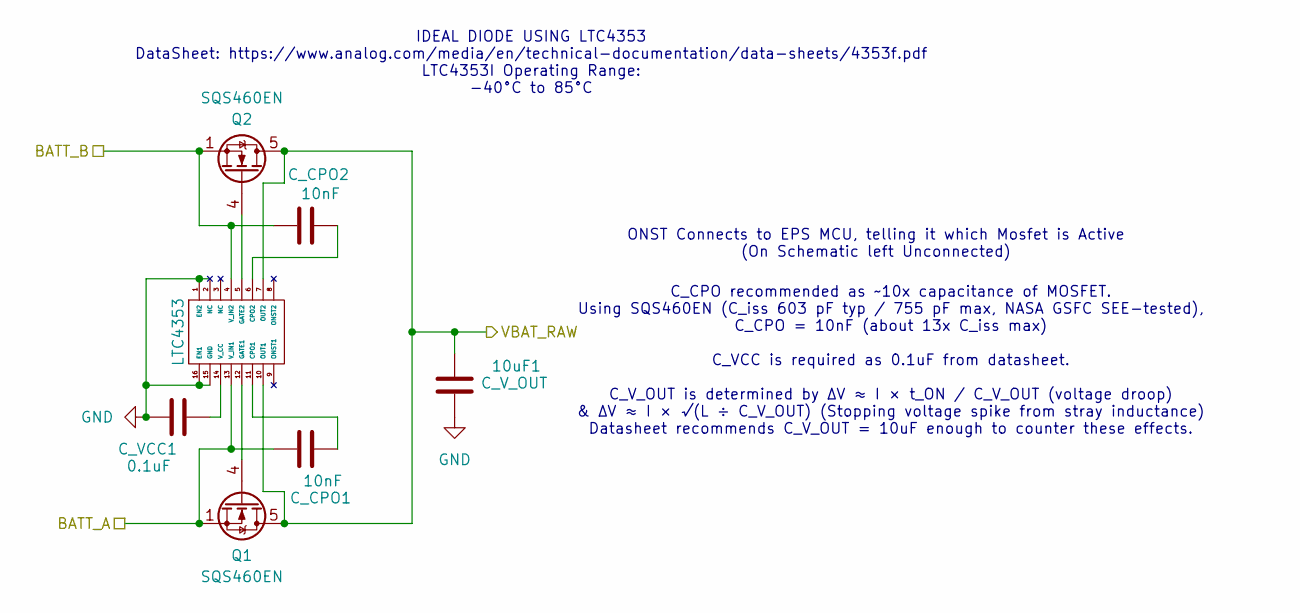
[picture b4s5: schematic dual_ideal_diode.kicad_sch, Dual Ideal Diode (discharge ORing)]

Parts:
10uF1: C_V_OUT; C_0805_2012Metric; MPN C2012X7S1E106K125AE; LCSC_PreFlight C15850
C_CPO1, C_CPO2: 10nF; C_0603_1608Metric; MPN CGA3E2X7R1H103K080AA; LCSC_PreFlight Verify at LCSC
C_VCC1: 0.1uF; C_0402_1005Metric; MPN GCM155R71H104KE02D; LCSC_PreFlight C1525
LTC4353: MSOP-16_3x4.039mm_P0.5mm; MPN LTC4353IMS#PBF; LCSC_PreFlight Not stocked at LCSC - order from DigiKe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
Q1, Q2: SQS460EN; Vishay_PowerPAK_1212-8_Single; MPN SQS460EN-T1_GE3; LCSC_PreFlight Verify at LCSC

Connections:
/Batteries/BATT_A: C_CPO1.2, LTC4353.13 (V_IN1), Q1.1 (S), Q1.2 (S), Q1.3 (S); also elsewhere on the board
/Batteries/BATT_B: C_CPO2.2, LTC4353.4 (V_IN2), Q2.1 (S), Q2.2 (S), Q2.3 (S); also elsewhere on the board
/Dual Ideal Diode (discharge ORing)/VBAT_RAW: 10uF1.1, LTC4353.7 (OUT2), LTC4353.10 (OUT1), Q1.5 (D), Q2.5 (D); also elsewhere on the board
GND: 10uF1.2, C_VCC1.1, LTC4353.1 (EN2), LTC4353.2 (NC), LTC4353.15 (GND), LTC4353.16 (EN1); also elsewhere on the board
unnamed: C_CPO1.1, LTC4353.11 (CPO1)
unnamed: C_CPO2.1, LTC4353.6 (CPO2)
unnamed: LTC4353.12 (GATE1), Q1.4 (G)
unnamed: LTC4353.5 (GATE2), Q2.4 (G)
unnamed: C_VCC1.2, LTC4353.14 (V_CC)

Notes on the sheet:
C_CPO recommended as ~10x capacitance of MOSFET. Using SQS460EN (C_iss 603 pF typ / 755 pF max, NASA GSFC SEE-tested), C_CPO = 10nF (about 13x C_iss max) C_VCC is required as 0.1uF from datasheet. C_V_OUT is determined by ΔV ≈ I × t_ON / C_V_OUT (voltage droop) & ΔV ≈ I × √(L ÷ C_V_OUT) (Stopping v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
IDEAL DIODE USING LTC4353 DataSheet: https://www.analog.com/media/en/technical-documentation/data-sheets/4353f.pdf LTC4353I Operating Range: −40°C to 85°C
ONST Connects to EPS MCU, telling it which Mosfet is Active (On Schematic left Unconnected)
